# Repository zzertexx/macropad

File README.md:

# macropad
4x4 Keyboard with Rotary Encoder

## What is it?
It is a basic keyboard made following tutorial from Hack Club Blueprint

## Why did I build it?
To teach my brother building stuff, I teamed with him and explained how to design PCB

## How to recreate it?
1. 3D Print enclosure
2. Buy parts and PCB
3. Solder parts
4. Assemble parts in enclosure
5. Flush firmware
6. Enjoy

## Bill of Materials
| Name | Price |
| --- | --- |
| MX Switch Buttons x16 | 1$ |
| XIAO RP2040 | 6$ |
| Diodes | 1$ |
| Rotary Encoder | 0.6$ |
| Total | 8.6$ |

## Images

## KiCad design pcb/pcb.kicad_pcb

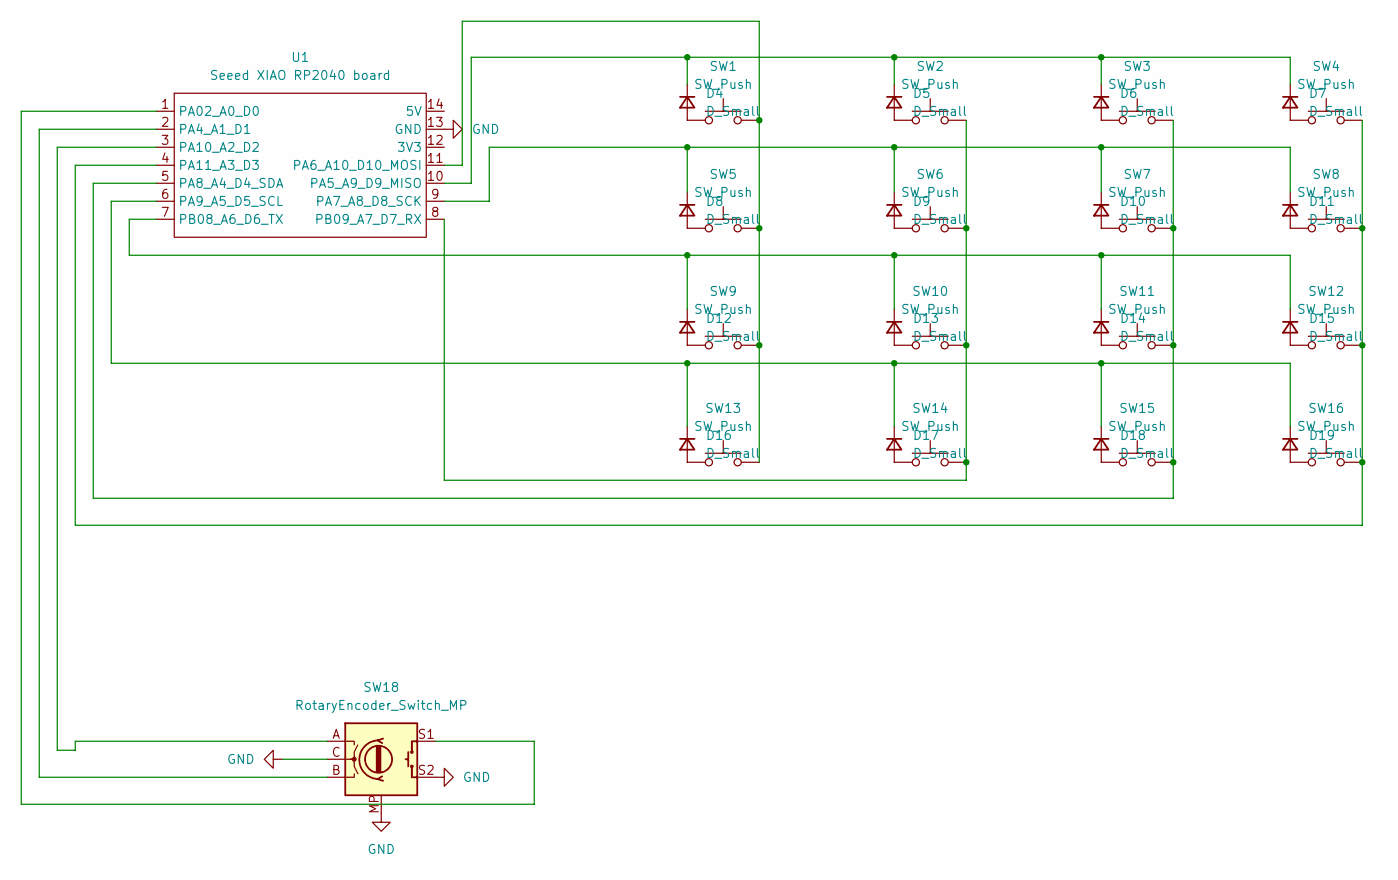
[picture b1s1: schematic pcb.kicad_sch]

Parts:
D4, D5, D6, D7, D8, D9, D10, D11, D12, D13, D14, D15, D16, D17, D18, D19: D_Small; SOD-123_L2.8-W1.8-LS3.7-RD-1
SW1, SW2, SW3, SW4, SW5, SW6, SW7, SW8, SW9, SW10, SW11, SW12, SW13, SW14, SW15, SW16: SW_Push; SW_Cherry_MX_1.00u_Plate
SW18: RotaryEncoder_Switch_MP; RotaryEncoder_Alps_EC11E-Switch_Vertical_H20mm
U1: Seeed XIAO RP2040 board; XIAO-Generic-Hybrid-14P-2.54-21X17.8MM

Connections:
GND: SW18.C, SW18.MP, SW18.S2, U1.13 (GND)
unnamed: D4.2 (A), SW1.1
unnamed: D4.1 (K), D5.1 (K), D6.1 (K), D7.1 (K), U1.10 (PA5_A9_D9_MISO)
unnamed: D5.2 (A), SW2.1
unnamed: D6.2 (A), SW3.1
unnamed: D7.2 (A), SW4.1
unnamed: D8.2 (A), SW5.1
unnamed: D9.2 (A), SW6.1
unnamed: D10.2 (A), SW7.1
unnamed: D8.1 (K), D9.1 (K), D10.1 (K), D11.1 (K), U1.9 (PA7_A8_D8_SCK)
unnamed: D11.2 (A), SW8.1
unnamed: D12.2 (A), SW9.1
unnamed: D12.1 (K), D13.1 (K), D14.1 (K), D15.1 (K), U1.7 (PB08_A6_D6_TX)
unnamed: D13.2 (A), SW10.1
unnamed: D14.2 (A), SW11.1
unnamed: D15.2 (A), SW12.1
unnamed: D16.2 (A), SW13.1
unnamed: D16.1 (K), D17.1 (K), D18.1 (K), D19.1 (K), U1.6 (PA9_A5_D5_SCL)
unnamed: D17.2 (A), SW14.1
unnamed: D18.2 (A), SW15.1
unnamed: D19.2 (A), SW16.1
unnamed: SW18.S1, U1.1 (PA02_A0_D0)
unnamed: SW18.B, U1.2 (PA4_A1_D1)
unnamed: SW1.2, SW5.2, SW9.2, SW13.2, U1.11 (PA6_A10_D10_MOSI)
unnamed: SW3.2, SW7.2, SW11.2, SW15.2, U1.5 (PA8_A4_D4_SDA)
unnamed: SW18.A, U1.3 (PA10_A2_D2)
unnamed: SW4.2, SW8.2, SW12.2, SW16.2, U1.4 (PA11_A3_D3)
unnamed: SW2.2, SW6.2, SW10.2, SW14.2, U1.8 (PB09_A7_D7_RX)

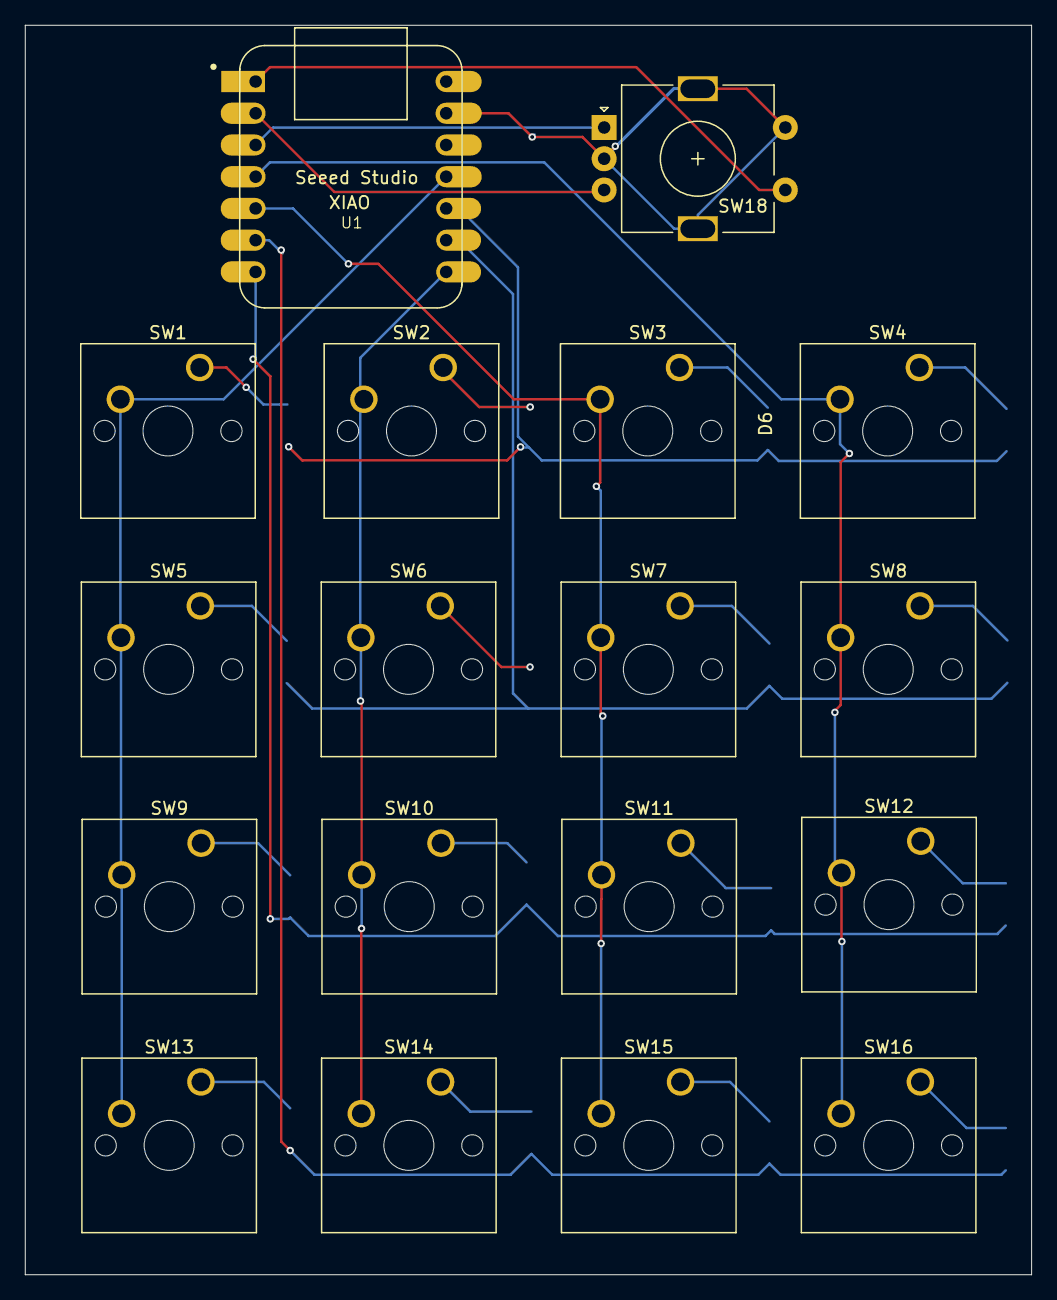
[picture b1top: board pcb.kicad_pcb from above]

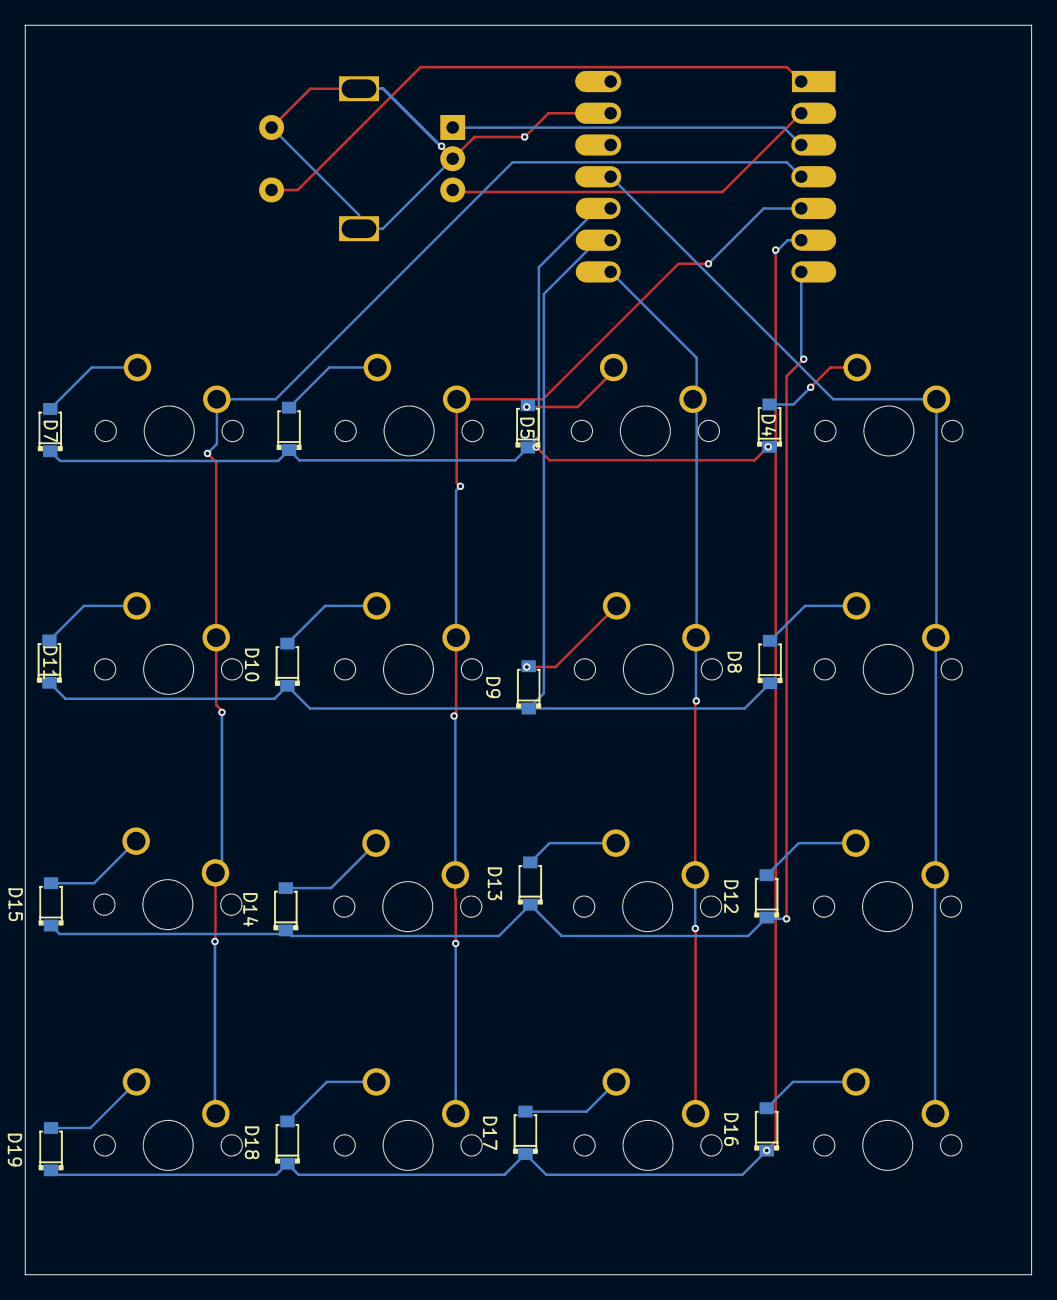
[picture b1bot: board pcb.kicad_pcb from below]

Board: 2 copper layers, 80.5 x 100.0 mm, 34 parts (16 on the bottom side), 28 nets.
